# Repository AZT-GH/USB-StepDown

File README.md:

# USB-StepDown
A buck converter + ldo that converts non power delivery USB (C to C compatible) to 3V3 and 1V8. 
Particularily useful for embedded development.

## Design Goals
I created this design so that I could test another board that required 3V3 and 1V8 inputs. (For use with PixArt PMW3360) Some of the key goals were for the pcb to be as compact as possible as I wanted to reuse portions of the schematic on other boards. I added schottky diodes at the expense of efficiency so that the board was not reliant on usb availability. This board can regulate up to 6v (~7v possible but not reccomended due to the LDO) to 3V3 and 1V8. The efficiency is not great due to the voltage drop of the diodes however this was not a priority for me as this board will only be used in a testing environment.

## Version History

V1 - Initial design ( not on repository :0 )

V1.1 - Fixed missing trace from feedback resistor to ground= and tidied up some trace paths.

## License

This project is licensed under the **CERN Open Hardware Licence – Strongly Reciprocal (CERN OHL-S)**.

By using, modifying, or distributing this hardware, you agree to comply with the terms of the CERN OHL-S v2.0.  
See the full license text in the [LICENSE](LICENSE.txt) file.

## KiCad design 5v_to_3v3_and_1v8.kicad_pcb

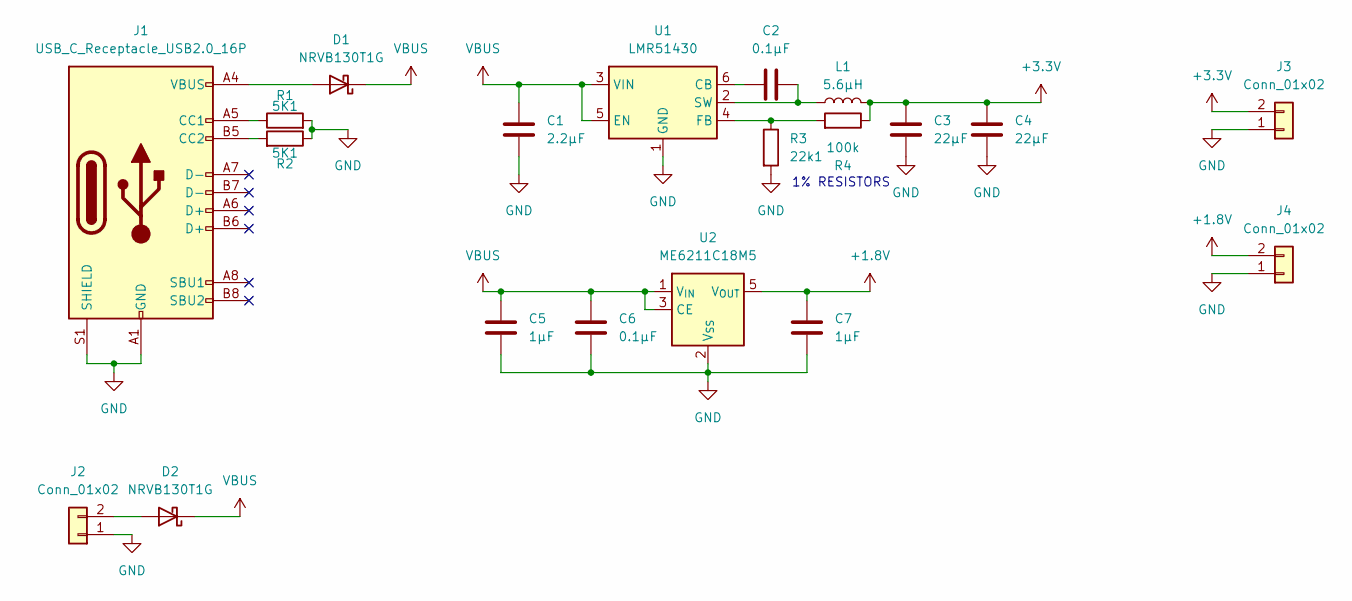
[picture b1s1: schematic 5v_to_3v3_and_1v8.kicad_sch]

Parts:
C1: 2.2µF; C_0805_2012Metric
C2, C6: 0.1µF; C_0805_2012Metric
C3, C4: 22µF; C_0805_2012Metric
C5, C7: 1µF; C_0805_2012Metric
D1, D2: NRVB130T1G; D_SOD-123
J1: USB_C_Receptacle_USB2.0_16P; USB_C_Receptacle_G-Switch_GT-USB-7010ASV
J2, J3, J4: Conn_01x02; PinHeader_1x02_P2.54mm_Vertical; Part Number 1-0201FBV0T
L1: 5.6µH; L_Cenker_CKCS3015
R1, R2: 5K1; R_0805_2012Metric
R3: 22k1; R_1206_3216Metric
R4: 100k; R_1206_3216Metric
U1: LMR51430; SOT-23-6
U2: ME6211C18M5; SOT-23-5

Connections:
+1.8V: C7.1, J4.2, U2.5 (V_{OUT})
+3.3V: C3.1, C4.1, J3.2, L1.2, R4.1
GND: C1.2, C3.2, C4.2, C5.2, C6.2, C7.2, J1.A1 (GND), J1.A12 (GND), J1.B1 (GND), J1.B12 (GND), J1.S1 (SHIELD), J2.1, J3.1, J4.1, R1.2, R2.1, R3.2, U1.1 (GND), U2.2 (V_{SS})
unnamed: D1.2 (A), J1.A4 (VBUS), J1.A9 (VBUS), J1.B4 (VBUS), J1.B9 (VBUS)
unnamed: D2.2 (A), J2.2
unnamed: J1.A5 (CC1), R1.1
unnamed: J1.B5 (CC2), R2.2
unnamed: C2.2, U1.6 (CB)
unnamed: R3.1, R4.2, U1.4 (FB)
unnamed: C2.1, L1.1, U1.2 (SW)
VBUS: C1.1, C5.1, C6.1, D1.1 (K), D2.1 (K), U1.3 (VIN), U1.5 (EN), U2.1 (V_{IN}), U2.3 (CE)

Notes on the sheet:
1% RESISTORS

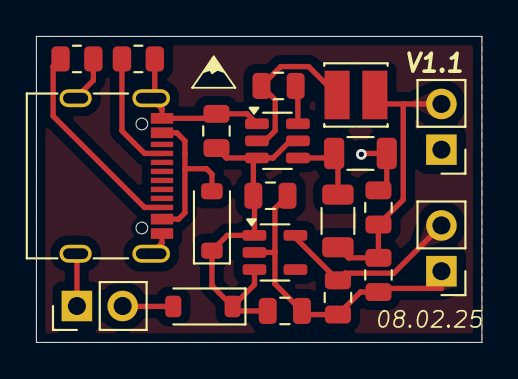
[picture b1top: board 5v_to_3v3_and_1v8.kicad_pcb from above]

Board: 2 copper layers, 24.8 x 17.0 mm, 20 parts (0 on the bottom side), 11 nets.

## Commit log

2025-03-15 Updated licensing
    Finished implementing CERN-OHL-S
